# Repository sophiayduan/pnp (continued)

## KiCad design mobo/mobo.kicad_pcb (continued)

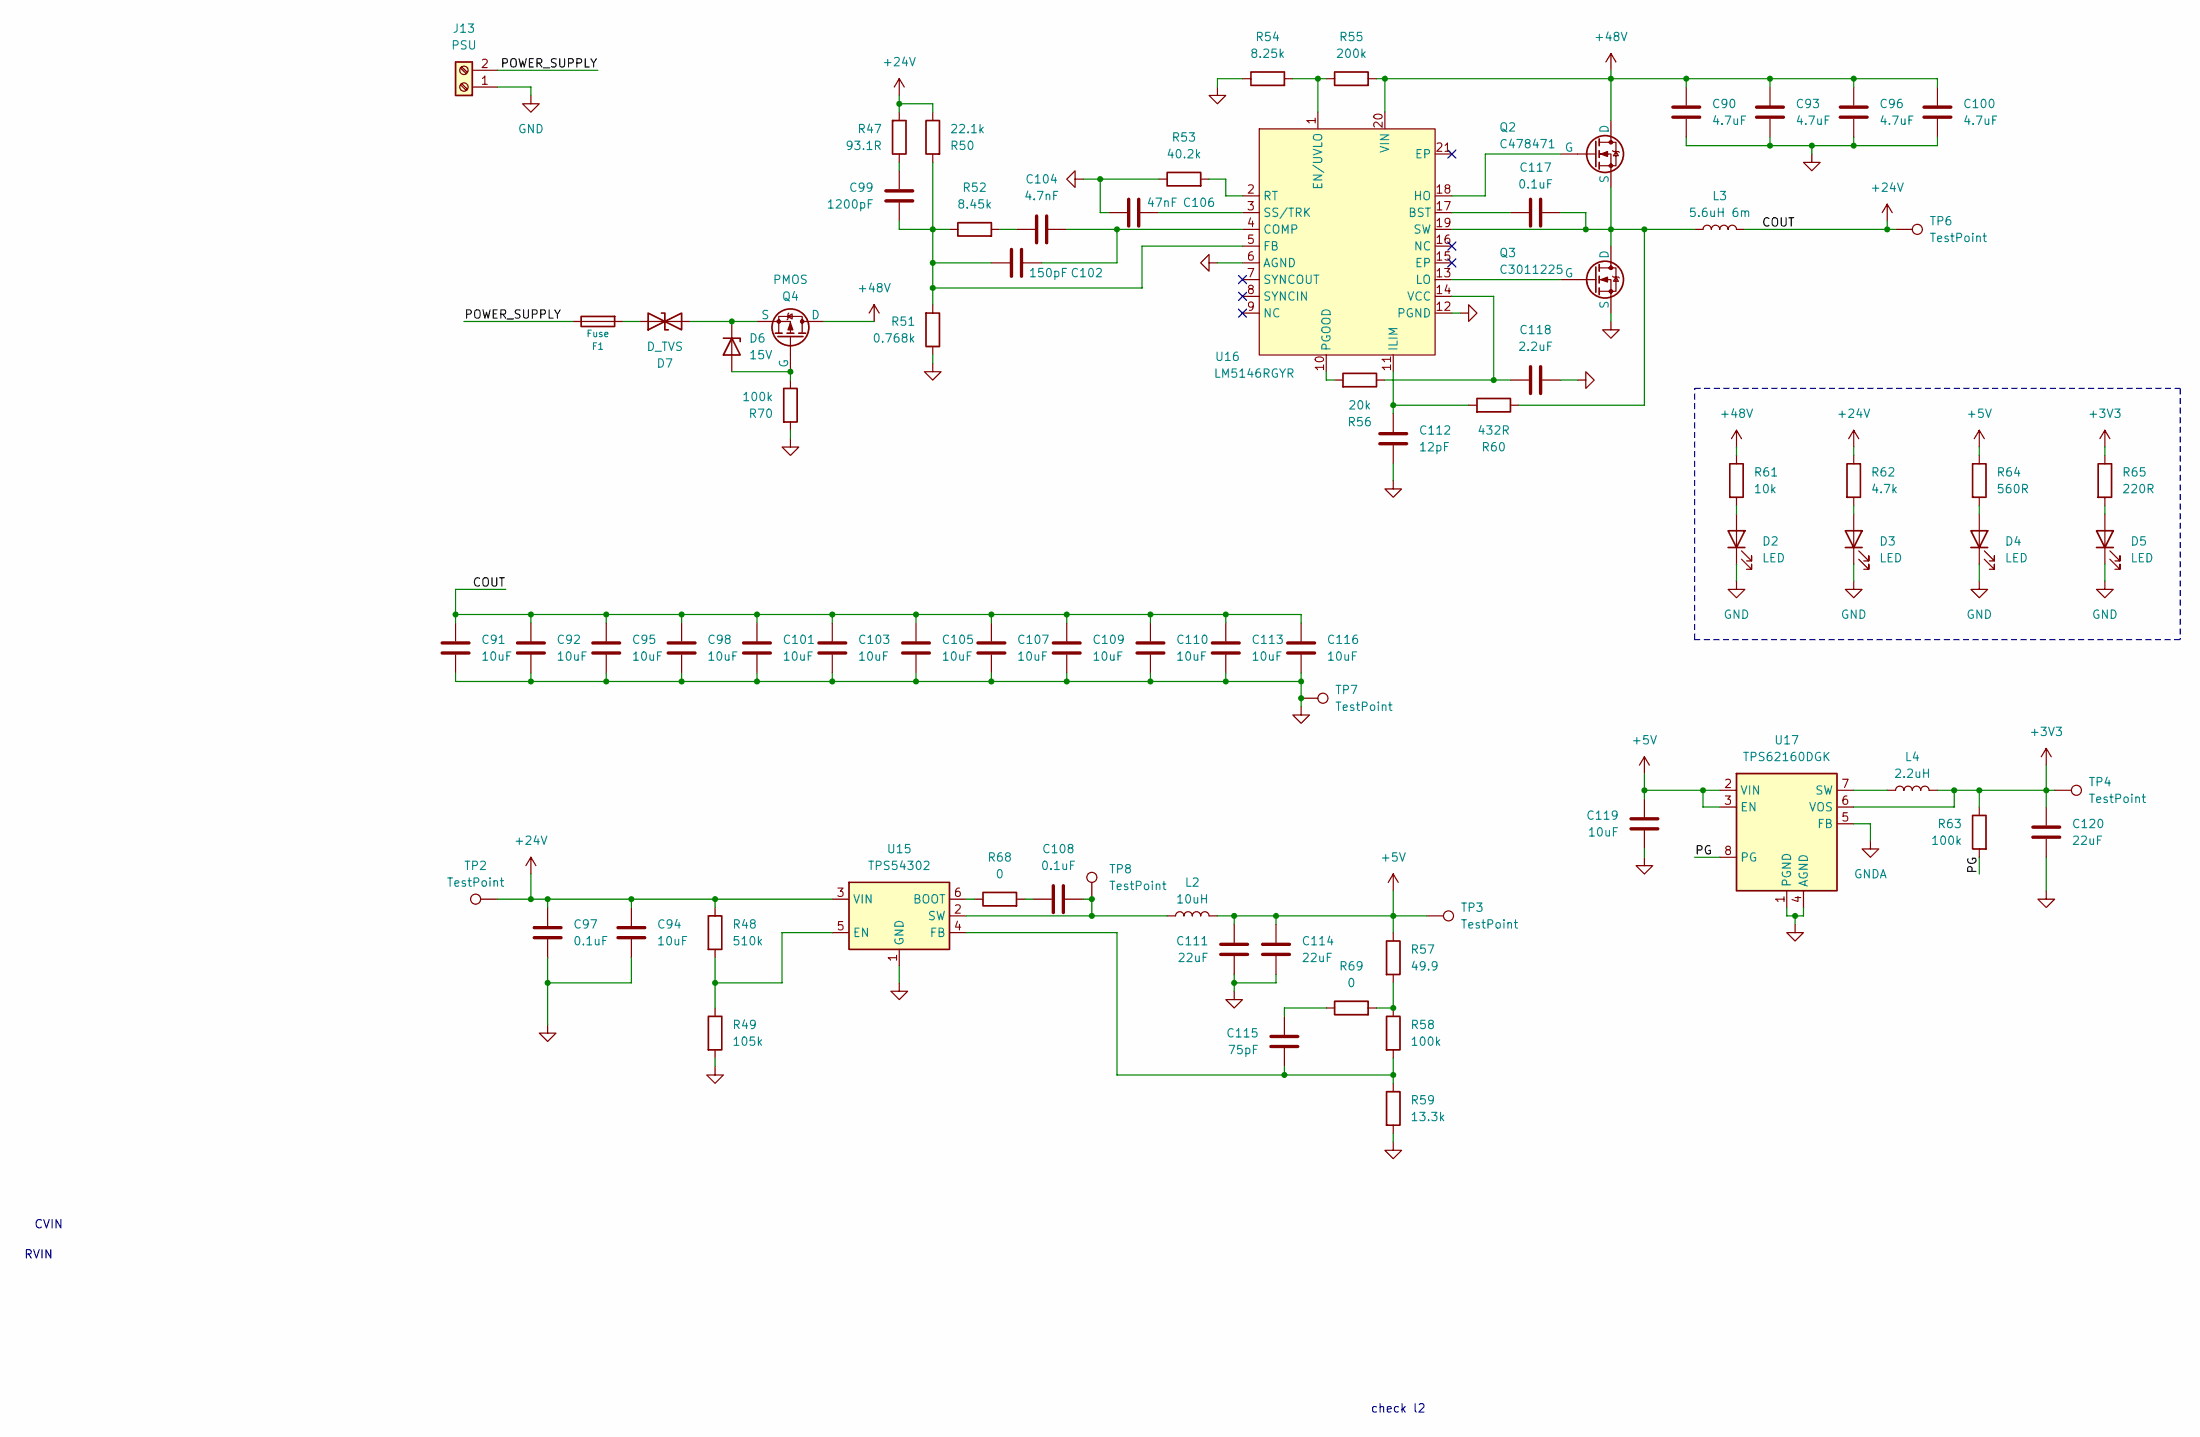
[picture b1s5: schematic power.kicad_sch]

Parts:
C90, C93, C96, C100: 4.7uF; C_1210_3225Metric
C91, C92, C94, C95, C98, C101, C103, C105, C107, C109, C110, C113, C116: 10uF; C_1210_3225Metric
C97, C108, C117: 0.1uF; C_0603_1608Metric
C99: 1200pF; C_0402_1005Metric
C102: 150pF; C_0402_1005Metric
C104: 4.7nF; C_0402_1005Metric
C106: 47nF; C_0603_1608Metric
C111, C114: 22uF; C_1210_3225Metric
C112: 12pF; C_0603_1608Metric
C115: 75pF; C_0603_1608Metric
C118: 2.2uF; C_0805_2012Metric
C119: 10uF; C_0805_2012Metric
C120: 22uF; C_0805_2012Metric
D2, D3, D4, D5: LED; LED_0805_2012Metric
D6: 15V; D_SOD-123F
D7: D_TVS; D_SMC
F1: Fuse; Fuseholder_Littelfuse_Nano2_154x; LCSC C206916
J13: PSU; TerminalBlock_Phoenix_MKDS-1,5-2-5.08_1x02_P5.08mm_Horizont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
L2: 10uH; L_SOREDE_SNR.1050_10x10x5mm
L3: 5.6uH 6m; L_Ferrocore_DLG-1004
L4: 2.2uH; L_APV_ANR3012
Q2: C478471; VSON-8_3.3x3.3mm_P0.65mm_NexFET
Q3: C3011225; PQFN-8-EP_6x5mm_P1.27mm_Generic
Q4: PMOS; TO-252-2_TabPin1
R47: 93.1R; R_0402_1005Metric
R48: 510k; R_0603_1608Metric
R49: 105k; R_0603_1608Metric
R50: 22.1k; R_0402_1005Metric
R51: 0.768k; R_0402_1005Metric
R52: 8.45k; R_0402_1005Metric
R53: 40.2k; R_0402_1005Metric
R54: 8.25k; R_0402_1005Metric
R55: 200k; R_0603_1608Metric
R56: 20k; R_0402_1005Metric
R57: 49.9; R_0603_1608Metric
R58, R63: 100k; R_0603_1608Metric
R59: 13.3k; R_0603_1608Metric
R60: 432R; R_0805_2012Metric
R61: 10k; R_1206_3216Metric
R62: 4.7k; R_0805_2012Metric
R64: 560R; R_0603_1608Metric
R65: 220R; R_0603_1608Metric
R68, R69: 0; R_0603_1608Metric
R70: 100k; R_0402_1005Metric
TP2, TP3, TP4, TP6, TP7, TP8: TestPoint; TestPoint_Pad_D2.0mm
U15: TPS54302; SOT-23-6
U16: LM5146RGYR; VQFN-20_L4.5-W3.5-P0.50-BL-EP; MPN LM5146RGYR; LCSC Part C3188679
U17: TPS62160DGK; MSOP-8_3x3mm_P0.65mm

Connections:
+3V3: C120.1, L4.2, R63.1, R65.1, TP4.1, U17.6 (VOS); also elsewhere on the board
+5V: C111.2, C114.2, C119.1, L2.2, R57.1, R64.1, TP3.1, U17.2 (VIN), U17.3 (EN); also elsewhere on the board
+24V: C91.1, C92.1, C94.1, C95.1, C97.1, C98.1, C101.1, C103.1, C105.1, C107.1, C109.1, C110.1, C113.1, C116.1, L3.2, R47.2, R48.1, R50.1, R62.1, TP2.1, TP6.1, U15.3 (VIN); also elsewhere on the board
+48V: C90.1, C93.1, C96.1, C100.1, Q2.1 (D), Q4.1 (D), R55.2, R61.1, U16.20 (VIN)
/Power/PG: R63.2, U17.8 (PG)
/Power/POWER_SUPPLY: F1.1, J13.2
GND: C90.2, C91.2, C92.2, C93.2, C94.2, C95.2, C96.2, C97.2, C98.2, C100.2, C101.2, C103.2, C105.2, C106.1, C107.2, C109.2, C110.2, C111.1, C112.2, C113.2, C114.1, C116.2, C118.2, C119.2, C120.2, D2.1 (K), D3.1 (K), D4.1 (K), D5.1 (K), J13.1, Q3.3 (S), R49.2, R51.1, R53.1, R54.1, R59.2, R70.2, TP7.1, U15.1 (GND), U16.6 (AGND), U16.12 (PGND), U17.1 (PGND), U17.4 (AGND); also elsewhere on the board
GNDA: U17.5 (FB)
unnamed: C99.1, R47.1
unnamed: C104.1, R52.2
unnamed: C108.1, R68.2
unnamed: C115.2, R69.1
unnamed: D2.2 (A), R61.2
unnamed: D3.2 (A), R62.2
unnamed: D4.2 (A), R64.2
unnamed: D5.2 (A), R65.2
unnamed: D6.2 (A), Q4.2 (G), R70.1
unnamed: D6.1 (K), D7.2 (A2), Q4.3 (S)
unnamed: D7.1 (A1), F1.2
unnamed: Q2.2 (G), U16.18 (HO)
unnamed: C117.1, L3.1, Q2.3 (S), Q3.1 (D), R60.1, U16.19 (SW)
unnamed: Q3.2 (G), U16.13 (LO)
unnamed: R57.2, R58.1, R69.2
unnamed: R68.1, U15.6 (BOOT)
unnamed: R48.2, R49.1, U15.5 (EN)
unnamed: C115.1, R58.2, R59.1, U15.4 (FB)
unnamed: C108.2, L2.1, TP8.1, U15.2 (SW)
unnamed: C117.2, U16.17 (BST)
unnamed: C102.1, C104.2, U16.4 (COMP)
unnamed: R54.2, R55.1, U16.1 (EN/UVLO)
unnamed: C99.2, C102.2, R50.2, R51.2, R52.1, U16.5 (FB)
unnamed: C112.1, R60.2, U16.11 (ILIM)
unnamed: R56.2, U16.10 (PGOOD)
unnamed: R53.2, U16.2 (RT)
unnamed: C106.2, U16.3 (SS/TRK)
unnamed: C118.1, R56.1, U16.14 (VCC)
unnamed: L4.1, U17.7 (SW)

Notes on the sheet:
check l2
CVIN
RVIN

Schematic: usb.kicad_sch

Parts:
J6: USB_C_Receptacle_USB2.0_14P; USB_C_Receptacle_HRO_TYPE-C-31-M-12
R6, R7: 5.1k; R_0402_1005Metric

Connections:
+5V: J6.A4 (VBUS), J6.A9 (VBUS), J6.B4 (VBUS), J6.B9 (VBUS); also elsewhere on the board
/MCU - IO/D+: J6.A6 (D+), J6.B6 (D+); also elsewhere on the board
/MCU - IO/D-: J6.A7 (D-), J6.B7 (D-); also elsewhere on the board
GND: J6.A1 (GND), J6.A12 (GND), J6.B1 (GND), J6.B12 (GND), J6.S1 (SHIELD), R6.2, R7.2; also elsewhere on the board
unnamed: J6.A5 (CC1), R6.1
unnamed: J6.B5 (CC2), R7.1

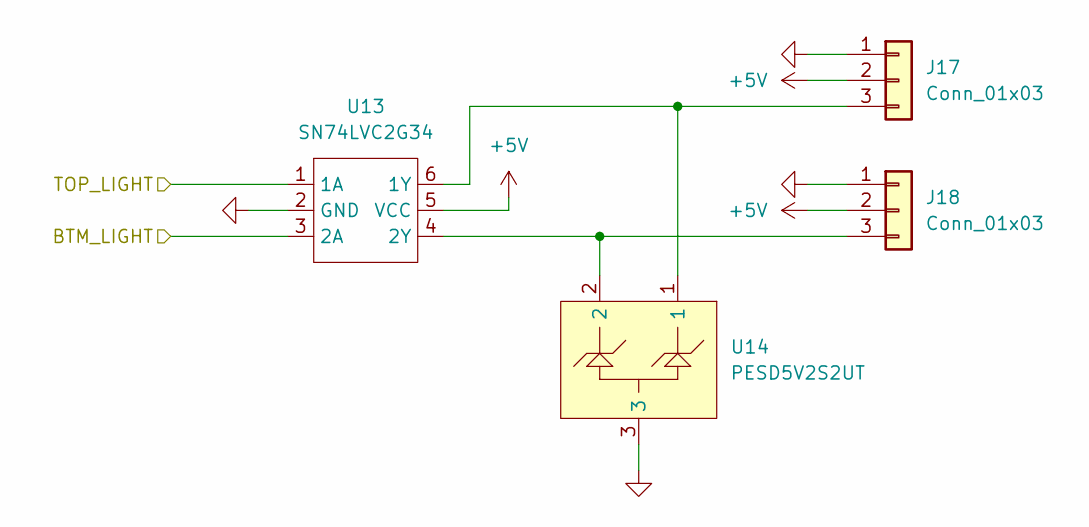
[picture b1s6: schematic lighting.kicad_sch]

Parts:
J17, J18: Conn_01x03; JST_PH_B3B-PH-SM4-TB_1x03-1MP_P2.00mm_Vertical
U13: SN74LVC2G34; SOT-23-6; JLCPCB C347589
U14: PESD5V2S2UT; SOT-23-3; JLCPCB C2827690

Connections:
+5V: J17.2, J18.2, U13.5 (VCC); also elsewhere on the board
/Lighting/BTM_LIGHT: U13.3 (2A); also elsewhere on the board
/Lighting/TOP_LIGHT: U13.1 (1A); also elsewhere on the board
GND: J17.1, J18.1, U13.2 (GND), U14.3; also elsewhere on the board
unnamed: J17.3, U13.6 (1Y), U14.1
unnamed: J18.3, U13.4 (2Y), U14.2

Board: 4 copper layers, 249 parts (0 on the bottom side), 225 nets, no tracks yet.

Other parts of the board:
H5#2: MountingHole_Pad; MountingHole_2.2mm_M2_Pad_Via

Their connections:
GND: H5#2.1; also elsewhere on the board

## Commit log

2026-03-29 set up obsidian vault
2026-03-29 add .obsidian
2026-03-29 ignore JOURNAL.md
2026-03-29 stop tracking JOURNAL.md
2026-04-01 journals
2026-04-19 Add 'journals/' to .gitignore
2026-04-28 remove ignored items
2026-05-25 update .gitignore for kicad files
2026-05-25 mobo v1, 1 unit
